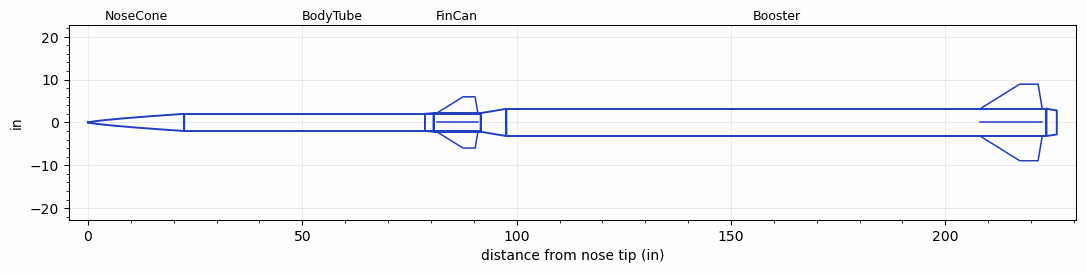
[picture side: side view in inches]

<RASAeroDocument>
 <FileVersion>2</FileVersion>
 <RocketDesign>
  <NoseCone>
   <Length>22.44</Length>
   <Diameter>4</Diameter>
   <Shape>Power Law</Shape>
   <BluntRadius>0.0825</BluntRadius>
   <Location>0</Location>
   <PowerLaw>0.75</PowerLaw>
  </NoseCone>
  <BodyTube>
   <Length>69.16</Length>
   <Diameter>4</Diameter>
   <Location>22.44</Location>
  </BodyTube>
  <FinCan>
   <Length>11</Length>
   <Diameter>4.35</Diameter>
   <InsideDiameter>4</InsideDiameter>
   <Location>91.60001</Location>
   <ShoulderLength>2</ShoulderLength>
   <Offset>-11</Offset>
   <Fin>
    <Count>4</Count>
    <Chord>9.57</Chord>
    <Span>3.8</Span>
    <SweepDistance>6.105</SweepDistance>
    <TipChord>2.84</TipChord>
    <Thickness>0.25</Thickness>
    <LERadius>0.08</LERadius>
    <Location>10.23</Location>
    <AirfoilSection>Hexagonal</AirfoilSection>
    <FX1>0.5</FX1>
    <FX3>0.5</FX3>
   </Fin>
  </FinCan>
  <Booster>
   <Length>126</Length>
   <Diameter>6.35</Diameter>
   <InsideDiameter>4.35</InsideDiameter>
   <Location>91.60001</Location>
   <ShoulderLength>6</ShoulderLength>
   <BoattailLength>2.4</BoattailLength>
   <BoattailRearDiameter>5.6</BoattailRearDiameter>
   <Fin>
    <Count>4</Count>
    <Chord>14.5</Chord>
    <Span>5.75</Span>
    <SweepDistance>9.25</SweepDistance>
    <TipChord>4.3</TipChord>
    <Thickness>0.25</Thickness>
    <LERadius>0.08</LERadius>
    <Location>15.5</Location>
    <AirfoilSection>Hexagonal</AirfoilSection>
    <FX1>0.5</FX1>
    <FX3>0.5</FX3>
   </Fin>
  </Booster>
  <Surface>Cast Iron (Very Rough)</Surface>
  <ModifiedBarrowman>True</ModifiedBarrowman>
  <Turbulence>True</Turbulence>
  <UseBooster1>False</UseBooster1>
  <UseBooster2>False</UseBooster2>
 </RocketDesign>
 <LaunchSite>
  <Altitude>3000</Altitude>
  <Pressure>0</Pressure>
  <RodAngle>2</RodAngle>
  <RodLength>18</RodLength>
  <Temperature>85</Temperature>
  <WindSpeed>8</WindSpeed>
 </LaunchSite>
 <Recovery>
  <Altitude1>1000</Altitude1>
  <Altitude2>1000</Altitude2>
  <DeviceType1>None</DeviceType1>
  <DeviceType2>None</DeviceType2>
  <Event1>False</Event1>
  <Event2>False</Event2>
  <Size1>1</Size1>
  <Size2>1</Size2>
  <EventType1>None</EventType1>
  <EventType2>None</EventType2>
  <CD1>1.33</CD1>
  <CD2>1.33</CD2>
 </Recovery>
 <SimulationList>
  <Simulation>
   <SustainerEngine>O4400  (O4400)</SustainerEngine>
   <SustainerLaunchWt>58.2</SustainerLaunchWt>
   <SustainerNozzleDiameter>3.8</SustainerNozzleDiameter>
   <SustainerCG>54.3</SustainerCG>
   <SustainerIgnitionDelay>15</SustainerIgnitionDelay>
   <Booster1Engine>Q10000  (Q10000)</Booster1Engine>
   <Booster1LaunchWt>220.2</Booster1LaunchWt>
   <Booster1SeparationDelay>0</Booster1SeparationDelay>
   <Booster1IgnitionDelay>0</Booster1IgnitionDelay>
   <Booster1CG>118.37</Booster1CG>
   <Booster1NozzleDiameter>5.3</Booster1NozzleDiameter>
   <IncludeBooster1>True</IncludeBooster1>
   <Booster2Delay>0</Booster2Delay>
   <IncludeBooster2>False</IncludeBooster2>
   <TimetoApogee>187.8409</TimetoApogee>
   <MaxAltitude>462613.2</MaxAltitude>
   <MaxVelocity>5500.551</MaxVelocity>
  </Simulation>
 </SimulationList>
</RASAeroDocument>
